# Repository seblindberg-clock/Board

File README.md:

## Clock Board

## Revisions

Board revisions are kept as tags in git. The board is generally tagged when the files have been sent off for manufacturing. To export a specific revision, simply run

```
$ git archive --format zip -o /path/to/rev-a.zip 4d268f
```

where the hash of the tag can be found by running `git show rev-a` for the specific tag.

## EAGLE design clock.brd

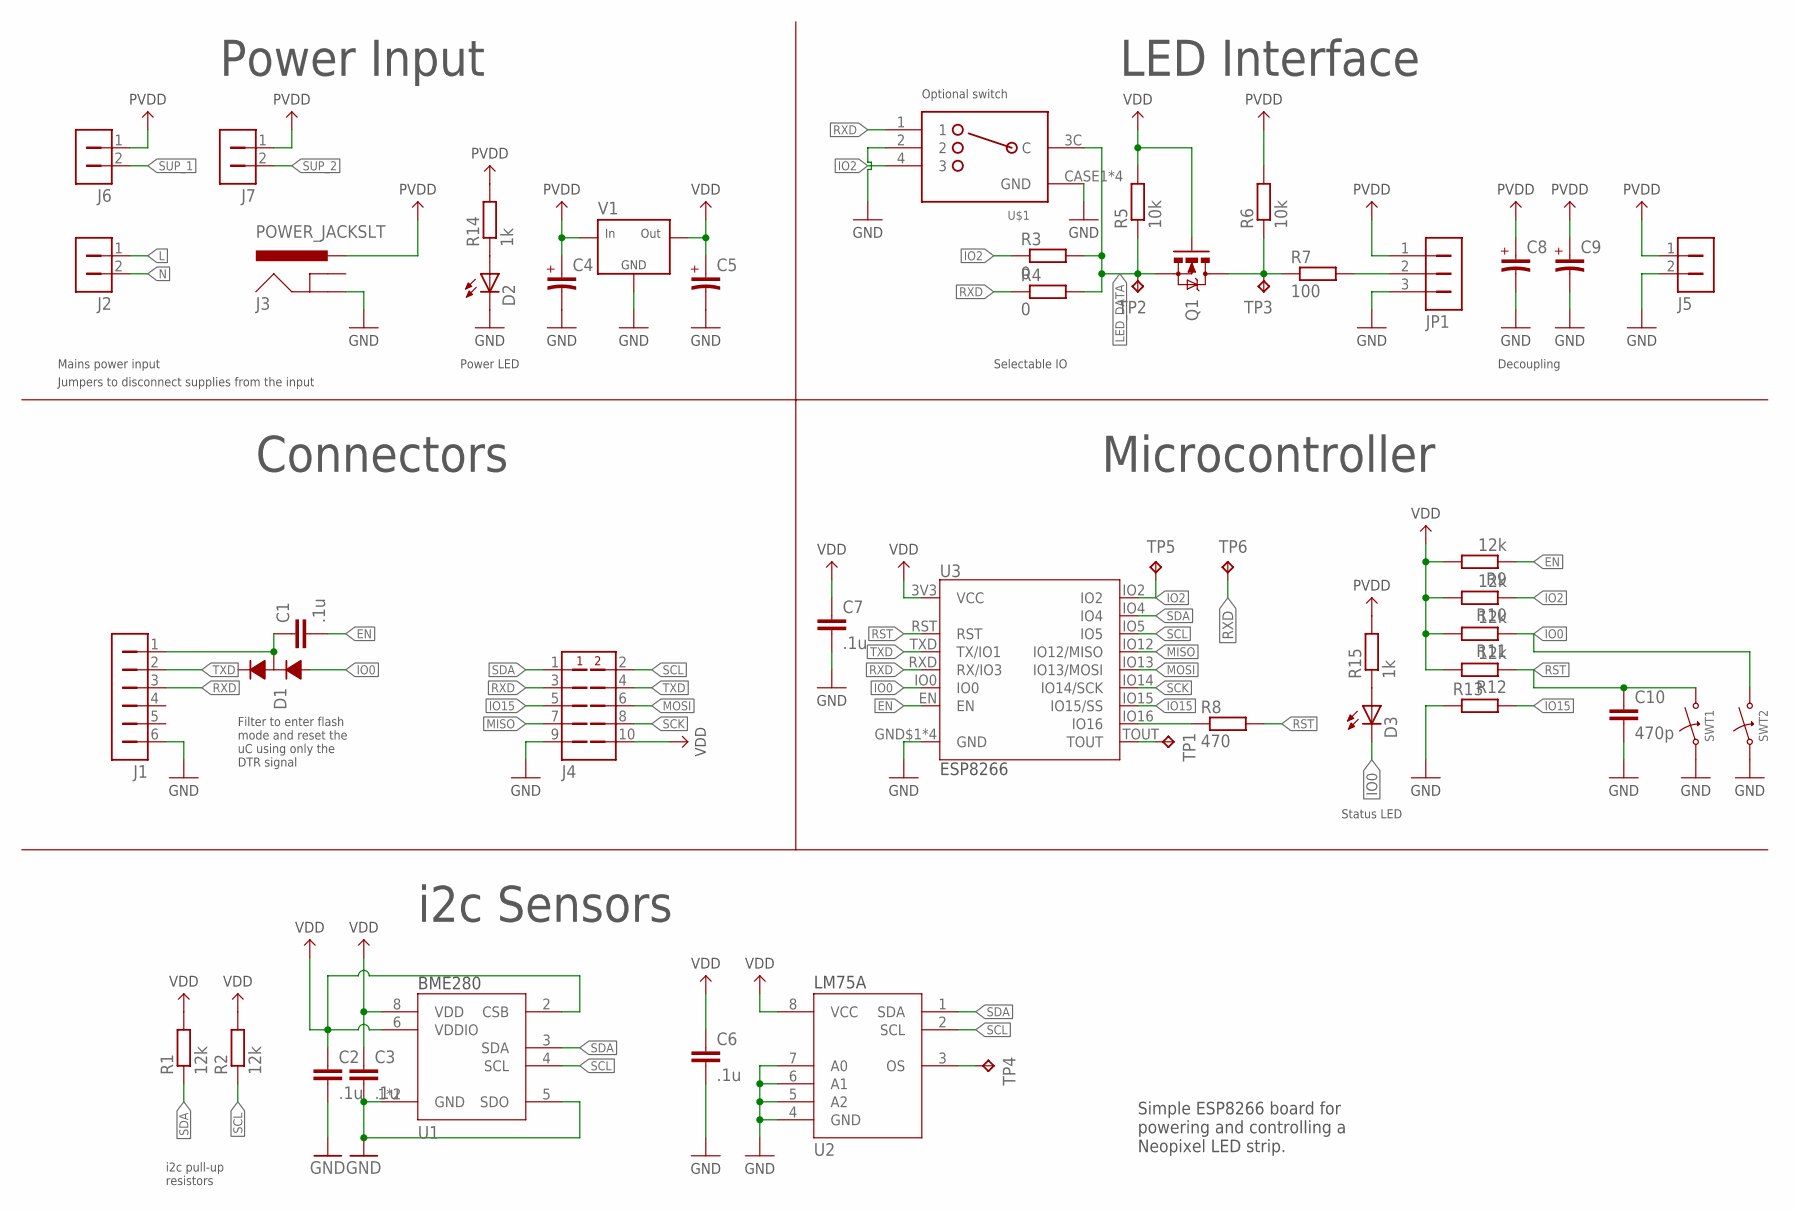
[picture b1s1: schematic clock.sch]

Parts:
C1, C2, C3, C6, C7: .1u; 0603
C4, C5: C_POL_1206; 1206_POL
C8, C9: C_POL_AVE_X; AVE_X
C10: 470p; 0603
D1: SBAV99WT1G; SC70
D2, D3: LED_0805; 0805_LED
J1: 1X6_RIGHT
J2: 1X2_IEC_C8_RIGHT; IEC_C8_RIGHT
J3: POWER_JACKSLT; POWER_JACK_SLOT
J4: 2X5
J5: 1X2_MOLEX_53254
J6, J7: 1X2
JP1: 1X3_MOLEX_53254
Q1: NMOS_2N7002; SOT23
R1, R2, R9, R10, R11, R12: 12k; 0603
R3, R4: 0; 0603
R5, R6: 10k; 0603
R7: 100; 0603
R8: 470; 0603
R13: R_0603; 0603
R14, R15: 1k; 0603
SWT1, SWT2: BUTTON_SMD_2P; BTN_SMD_2PIN
TP1, TP2, TP3, TP4, TP5, TP6: TPTP15R; TP15R
U1: BME280
U2: LM75A_SO8; SO8
U3: ESP8266_13; ESP13
U$1: SWITCH_1P3T_SSSS812201; SSSS812201
V1: NCP1117; TO252

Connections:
EN: C1.2, R9.1, U3.EN
GND: C2.2, C3.2, C4.2, C5.2, C6.2, C7.2, C8.- (2), C9.- (2), C10.2, D2.C, J1.6, J3.GND@2 (GND), J4.9, J5.2, JP1.3, R13.1, SWT1.1, SWT2.1, U1.1 (GND), U1.5 (SDO), U1.7 (GND), U2.4 (GND), U2.5 (A2), U2.6 (A1), U2.7 (A0), U3.GND$1 (GND), U3.GND$2 (GND), U3.GND$3 (GND), U3.GND$4 (GND), U$1.2, U$1.CASE1 (GND), U$1.CASE2 (GND), U$1.CASE3 (GND), U$1.CASE4 (GND), V1.1 (GND)
IO0: D1.1 (ANODE), D3.C, R11.1, SWT2.2, U3.IO0
IO2: R3.1, R10.1, TP5.TP, U3.IO2, U$1.4 (3)
IO15: J4.5, R13.2, U3.IO15 (IO15/SS)
L: J2.1
LED_DATA: Q1.2 (S), R3.2, R4.2, R5.1, TP2.TP, U$1.3C (C)
MISO: J4.7, U3.IO12 (IO12/MISO)
MOSI: J4.6, U3.IO13 (IO13/MOSI)
N: J2.2
unnamed: TP4.TP, U2.3 (OS)
unnamed: Q1.3 (D), R6.1, R7.1, TP3.TP
unnamed: JP1.2, R7.2
unnamed: D2.A, R14.1
unnamed: D3.A, R15.1
unnamed: TP1.TP, U3.TOUT
unnamed: R8.1, U3.IO16
unnamed: C1.1, D1.3 (MIDDLE), J1.1
PVDD: C4.1, C8.+ (1), C9.+ (1), J3.PWR, J5.1, J6.1, J7.1, JP1.1, R6.2, R14.2, R15.2, V1.2 (IN)
RST: C10.1, R8.2, R12.1, SWT1.2, U3.RST
RXD: J1.3, J4.3, R4.1, TP6.TP, U3.RXD (RX/IO3), U$1.1
SCK: J4.8, U3.IO14 (IO14/SCK)
SCL: J4.2, R2.1, U1.4 (SCL), U2.2 (SCL), U3.IO5
SDA: J4.1, R1.1, U1.3 (SDA), U2.1 (SDA), U3.IO4
SUP_1: J6.2
SUP_2: J7.2
TXD: J1.2, J4.4, U3.TXD (TX/IO1)
VDD: C2.1, C3.1, C5.1, C6.1, C7.1, J4.10, Q1.1 (G), R1.2, R2.2, R5.2, R9.2, R10.2, R11.2, R12.2, U1.2 (CSB), U1.6 (VDDIO), U1.8 (VDD), U2.8 (VCC), U3.3V3 (VCC), V1.3 (OUT)

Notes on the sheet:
Selectable IO
LED Interface
Power Input
i2c Sensors
i2c pull-up resistors
Microcontroller
Connectors
Filter to enter flash mode and reset the uC using only the DTR signal
Simple ESP8266 board for powering and controlling a Neopixel LED strip.
Mains power input
Optional switch
Power LED
Decoupling
Status LED
Jumpers to disconnect supplies from the input

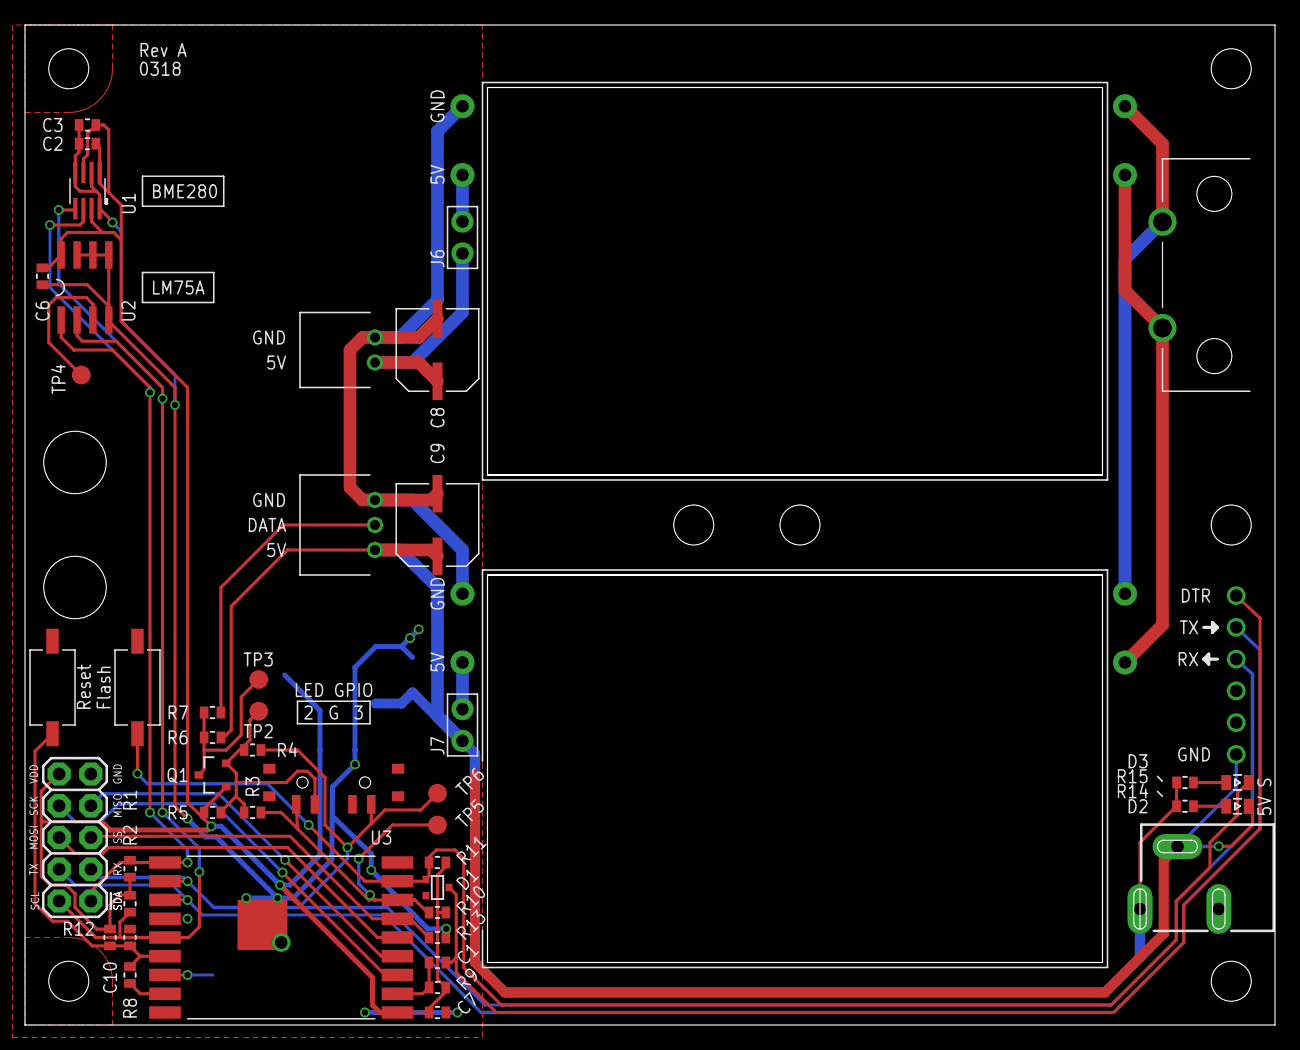
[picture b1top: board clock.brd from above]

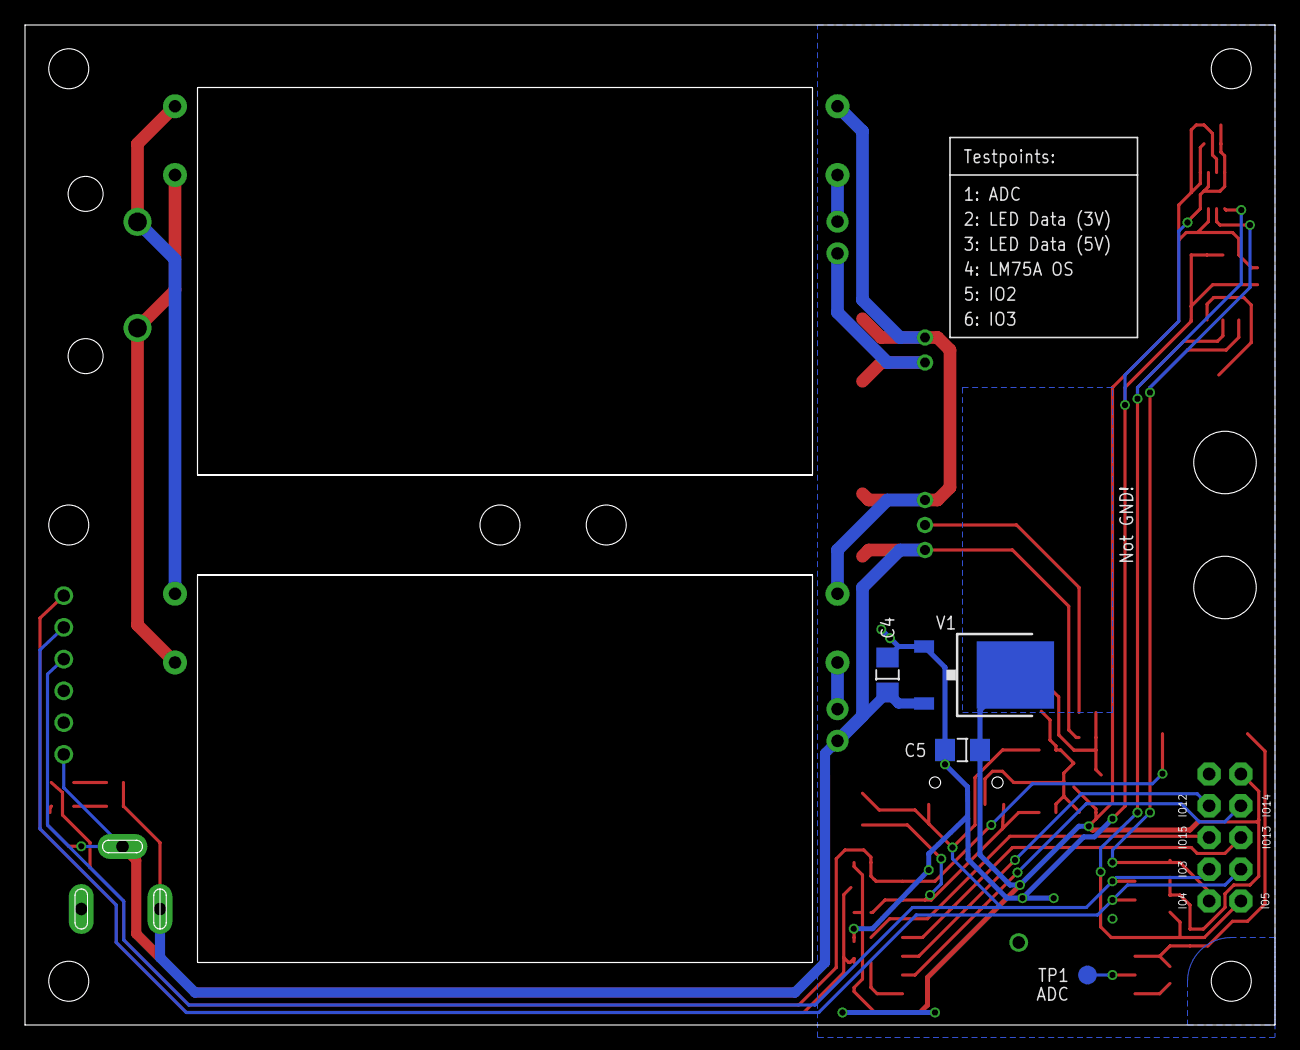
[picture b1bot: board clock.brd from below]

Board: 2 copper layers, 100.0 x 80.0 mm, 50 parts (4 on the bottom side), 24 nets.

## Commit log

2018-01-09 Initial commit, starting from rev B
2018-01-09 Added readme. The tag hash is not correct as the tag does not yet exist
2018-01-09 Added some measurements
2018-01-09 Added a power led and some silkscreen to make the footprints for the temperature sensors more obvious
2018-01-09 Changed revision since rev A was never actually ordered and tested
2018-01-09 Removed note about the old rev A
2018-03-15 Added a status LED to IO0
2018-03-15 Increased the safety margin between the live side of the power supply and the isolated 5 v rail
2018-03-15 Added testpoints to IO2 and IO3
2018-03-15 Worked on the silk
2018-03-15 Switched to the new footprint for the ESP8266
2018-03-15 Added silk and milling around the cutouts, just to be clear

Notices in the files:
parts and their libraries:
SparkFun-Connectors: Licensing: CC v3.0 Share-Alike You are welcome to use this library for commercial purposes.
